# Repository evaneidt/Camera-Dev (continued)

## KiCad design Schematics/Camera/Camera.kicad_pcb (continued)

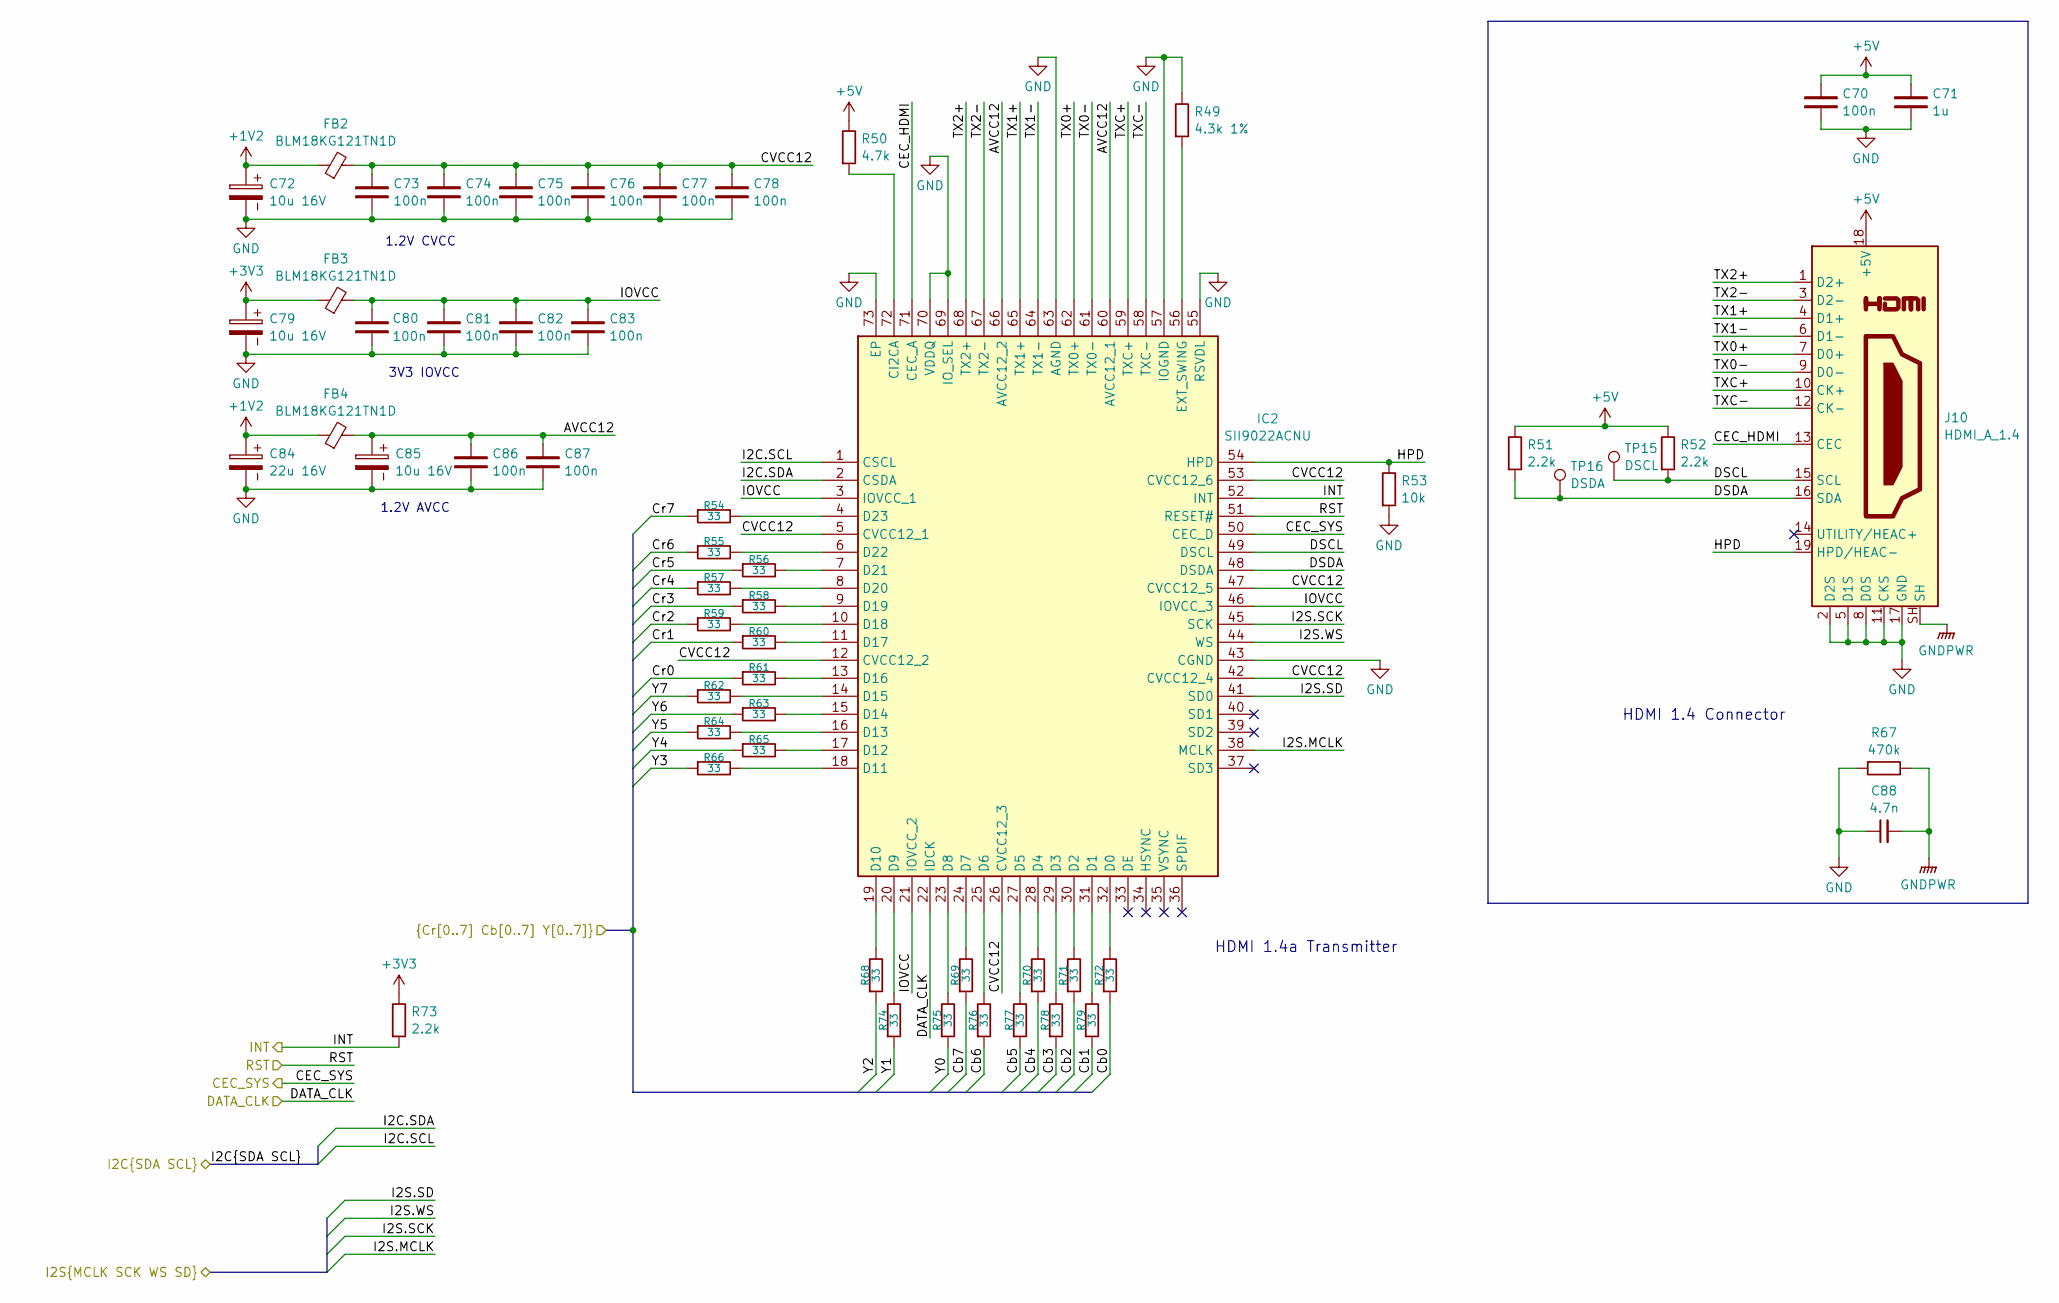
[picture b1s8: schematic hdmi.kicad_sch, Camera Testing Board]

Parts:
C70: 100n; C_0603_1608Metric
C71: 1u; C_0603_1608Metric
C72, C79, C85: 10u 16V; CP_EIA-3216-18_Kemet-A
C73, C74, C75, C76, C77, C78, C80, C81, C82, C83, C86, C87: 100n; C_0402_1005Metric
C84: 22u 16V; CP_EIA-3528-21_Kemet-B
C88: 4.7n; C_0603_1608Metric
FB2, FB3, FB4: BLM18KG121TN1D; L_0603_1608Metric
IC2: SII9022ACNU; QFN50P1000X1000X90-73N-D; Manufacturer_Part_Number SII9022ACNU
J10: HDMI_A_1.4; AMPHENOL_10029449-111RLF
R49: 4.3k 1%; R_0603_1608Metric
R50: 4.7k; R_0603_1608Metric
R51, R52, R73: 2.2k; R_0603_1608Metric
R53: 10k; R_0603_1608Metric
R54, R55, R56, R57, R58, R59, R60, R61, R62, R63, R64, R65, R66, R68, R69, R70, R71, R72, R74, R75, R76, R77, R78, R79: 33; R_0201_0603Metric
R67: 470k; R_0603_1608Metric
TP15: DSCL; TestPoint_Keystone_5000-5004_Miniature
TP16: DSDA; TestPoint_Keystone_5000-5004_Miniature

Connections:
+1V2: C72.1, C84.1, FB2.1, FB4.1; also elsewhere on the board
+3V3: C79.1, FB3.1, R73.2; also elsewhere on the board
+5V: C70.2, C71.2, J10.18 (+5V), R50.2, R51.2, R52.2; also elsewhere on the board
/HDMI/AVCC12: C85.1, C86.2, C87.2, FB4.2, IC2.60 (AVCC12_1), IC2.66 (AVCC12_2)
/HDMI/CEC_HDMI: IC2.71 (CEC_A), J10.13 (CEC)
/HDMI/CEC_SYS: IC2.50 (CEC_D); also elsewhere on the board
/HDMI/CVCC12: C73.2, C74.2, C75.2, C76.2, C77.2, C78.2, FB2.2, IC2.5 (CVCC12_1), IC2.12 (CVCC12_2), IC2.26 (CVCC12_3), IC2.42 (CVCC12_4), IC2.47 (CVCC12_5), IC2.53 (CVCC12_6)
/HDMI/Cb0: R72.1; also elsewhere on the board
/HDMI/Cb1: R79.1; also elsewhere on the board
/HDMI/Cb2: R71.1; also elsewhere on the board
/HDMI/Cb3: R78.1; also elsewhere on the board
/HDMI/Cb4: R70.1; also elsewhere on the board
/HDMI/Cb5: R77.1; also elsewhere on the board
/HDMI/Cb6: R76.1; also elsewhere on the board
/HDMI/Cb7: R69.1; also elsewhere on the board
/HDMI/Cr0: R61.1; also elsewhere on the board
/HDMI/Cr1: R60.1; also elsewhere on the board
/HDMI/Cr2: R59.1; also elsewhere on the board
/HDMI/Cr3: R58.1; also elsewhere on the board
/HDMI/Cr4: R57.1; also elsewhere on the board
/HDMI/Cr5: R56.1; also elsewhere on the board
/HDMI/Cr6: R55.1; also elsewhere on the board
/HDMI/Cr7: R54.1; also elsewhere on the board
/HDMI/DATA_CLK: IC2.22 (IDCK); also elsewhere on the board
/HDMI/DSCL: IC2.49 (DSCL), J10.15 (SCL), R52.1, TP15.1
/HDMI/DSDA: IC2.48 (DSDA), J10.16 (SDA), R51.1, TP16.1
/HDMI/HPD: IC2.54 (HPD), J10.19 (HPD/HEAC-), R53.2
/HDMI/I2C.SCL: IC2.1 (CSCL); also elsewhere on the board
/HDMI/I2C.SDA: IC2.2 (CSDA); also elsewhere on the board
/HDMI/I2S.MCLK: IC2.38 (MCLK); also elsewhere on the board
/HDMI/I2S.SCK: IC2.45 (SCK); also elsewhere on the board
/HDMI/I2S.SD: IC2.41 (SD0); also elsewhere on the board
/HDMI/I2S.WS: IC2.44 (WS); also elsewhere on the board
/HDMI/INT: IC2.52 (INT), R73.1; also elsewhere on the board
/HDMI/IOVCC: C80.2, C81.2, C82.2, C83.2, FB3.2, IC2.3 (IOVCC_1), IC2.21 (IOVCC_2), IC2.46 (IOVCC_3)
/HDMI/RST: IC2.51 (RESET#); also elsewhere on the board
/HDMI/TX0+: IC2.62 (TX0+), J10.7 (D0+)
/HDMI/TX0-: IC2.61 (TX0-), J10.9 (D0-)
/HDMI/TX1+: IC2.65 (TX1+), J10.4 (D1+)
/HDMI/TX1-: IC2.64 (TX1-), J10.6 (D1-)
/HDMI/TX2+: IC2.68 (TX2+), J10.1 (D2+)
/HDMI/TX2-: IC2.67 (TX2-), J10.3 (D2-)
/HDMI/TXC+: IC2.59 (TXC+), J10.10 (CK+)
/HDMI/TXC-: IC2.58 (TXC-), J10.12 (CK-)
/HDMI/Y0: R75.1; also elsewhere on the board
/HDMI/Y1: R74.1; also elsewhere on the board
/HDMI/Y2: R68.1; also elsewhere on the board
/HDMI/Y3: R66.1; also elsewhere on the board
/HDMI/Y4: R65.1; also elsewhere on the board
/HDMI/Y5: R64.1; also elsewhere on the board
/HDMI/Y6: R63.1; also elsewhere on the board
/HDMI/Y7: R62.1; also elsewhere on the board
GND: C70.1, C71.1, C72.2, C73.1, C74.1, C75.1, C76.1, C77.1, C78.1, C79.2, C80.1, C81.1, C82.1, C83.1, C84.2, C85.2, C86.1, C87.1, C88.1, IC2.43 (CGND), IC2.55 (RSVDL), IC2.57 (IOGND), IC2.63 (AGND), IC2.69 (IO_SEL), IC2.70 (VDDQ), IC2.73 (EP), J10.2 (D2S), J10.5 (D1S), J10.8 (D0S), J10.11 (CKS), J10.17 (GND), R49.2, R53.1, R67.1; also elsewhere on the board
GNDPWR: C88.2, J10.SH, R67.2; also elsewhere on the board
unnamed: IC2.72 (CI2CA), R50.1
unnamed: IC2.32 (D0), R72.2
unnamed: IC2.31 (D1), R79.2
unnamed: IC2.30 (D2), R71.2
unnamed: IC2.29 (D3), R78.2
unnamed: IC2.28 (D4), R70.2
unnamed: IC2.27 (D5), R77.2
unnamed: IC2.25 (D6), R76.2
unnamed: IC2.24 (D7), R69.2
unnamed: IC2.23 (D8), R75.2
unnamed: IC2.20 (D9), R74.2
unnamed: IC2.19 (D10), R68.2
unnamed: IC2.18 (D11), R66.2
unnamed: IC2.17 (D12), R65.2
unnamed: IC2.16 (D13), R64.2
unnamed: IC2.15 (D14), R63.2
unnamed: IC2.14 (D15), R62.2
unnamed: IC2.13 (D16), R61.2
unnamed: IC2.11 (D17), R60.2
unnamed: IC2.10 (D18), R59.2
unnamed: IC2.9 (D19), R58.2
unnamed: IC2.8 (D20), R57.2
unnamed: IC2.7 (D21), R56.2
unnamed: IC2.6 (D22), R55.2
unnamed: IC2.4 (D23), R54.2
unnamed: IC2.56 (EXT_SWING), R49.1

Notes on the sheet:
1.2V CVCC
HDMI 1.4a Transmitter
1.2V AVCC
HDMI 1.4 Connector
3V3 IOVCC

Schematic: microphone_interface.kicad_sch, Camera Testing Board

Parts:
C32, C33, C36: 100n; C_0603_1608Metric
C34, C35: 10u 16V; CP_EIA-3216-18_Kemet-A
D1, D2: LED; LED_0603_1608Metric
MK1, MK2: ICS-43434; InvenSense_ICS-43434-6_3.5x2.65mm
R21, R23: 0; R_0603_1608Metric
R22: 10k; R_0603_1608Metric
R24, R25, R26, R27: 33; R_0402_1005Metric
R28, R29: 470; R_0603_1608Metric
TP10: VBIAS; TestPoint_Keystone_5000-5004_Miniature
U7: PCM1780; SSOP-16_3.9x4.9mm_P0.635mm
U8: RCJ-2223; DUALRCA

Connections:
+3V3: C32.2, C33.2, MK1.5 (VDD), MK2.2 (LR), MK2.5 (VDD); also elsewhere on the board
+5V: C35.1, C36.2, U7.11 (Vcc); also elsewhere on the board
/HDMI/I2S.MCLK: R25.1; also elsewhere on the board
/HDMI/I2S.SCK: MK1.4 (SCK), MK2.4 (SCK), R24.1; also elsewhere on the board
/HDMI/I2S.SD: R21.2, R22.2, R23.2, R27.1; also elsewhere on the board
/HDMI/I2S.WS: MK1.1 (WS), MK2.1 (WS), R26.1; also elsewhere on the board
/Microcontroller/DAC.CLK: U7.3 (MC); also elsewhere on the board
/Microcontroller/DAC.MOSI: U7.4 (MD); also elsewhere on the board
/Microcontroller/DAC.nCS: U7.2 (~MS); also elsewhere on the board
/Microphone Interface/Audio Filtering/L_IN: U7.15 (V_{OUT}L); also elsewhere on the board
/Microphone Interface/Audio Filtering/L_OUT: U8.P$2 (BTM); also elsewhere on the board
/Microphone Interface/Audio Filtering/R_IN: U7.14 (V_{OUT}R); also elsewhere on the board
/Microphone Interface/Audio Filtering/R_OUT: U8.P$3 (TOP); also elsewhere on the board
/Microphone Interface/VBIAS: C34.1, TP10.1, U7.13 (V_{COM}); also elsewhere on the board
GND: C32.1, C33.1, C34.2, C35.2, C36.1, D1.1 (K), D2.1 (K), MK1.2 (LR), MK1.3 (GND), MK2.3 (GND), R22.1, U7.12 (AGND), U8.P$1 (GND); also elsewhere on the board
unnamed: D1.2 (A), R28.1
unnamed: D2.2 (A), R29.1
unnamed: MK1.6 (SD), R21.1
unnamed: MK2.6 (SD), R23.1
unnamed: R24.2, U7.7 (BCK)
unnamed: R27.2, U7.6 (DATA)
unnamed: R26.2, U7.8 (LRCK)
unnamed: R25.2, U7.5 (SCK)
unnamed: R29.2, U7.1 (ZEROL)
unnamed: R28.2, U7.16 (ZEROR)

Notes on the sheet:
f_s = 44.1 kHz I2S SCK = 64 * f_s = 2.8224 MHz DAC System Clock = MCLK = 256 * f_s = 11.290 MHz I2S WS = f_s = 44.1 kHz MIC STBY = I2S SCK < 200 kHz --> Pull WS & SCK to GND
Right Channel
Left Channel
Audio DAC
Red
I2S Signals
Microphones
RCA Audio Outputs
Clock Generation
Zero LEDs

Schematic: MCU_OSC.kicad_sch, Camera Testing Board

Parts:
C31: 100n; C_0603_1608Metric
X1: ECS-TXO-2520MV-500-AN-TR; Oscillator_SMD_ECS_2520MV-xxx-xx-4Pin_2.5x2.0mm
X2: ASEKDVAIG-32.768KHZ-KC-T3; Oscillator_SMD_Abracon_ASE-4Pin_3.2x2.5mm

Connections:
+3V3: C31.2, X1.1 (Tri-State), X1.4 (VDD), X2.1 (EN), X2.4 (Vdd); also elsewhere on the board
/Microcontroller/32.768kHz_OSC: X2.3 (OUT); also elsewhere on the board
/Microcontroller/50MHz_OSC: X1.3 (OUT); also elsewhere on the board
GND: C31.1, X1.2 (GND), X2.2 (GND); also elsewhere on the board

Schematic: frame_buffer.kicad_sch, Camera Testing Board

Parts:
C51, C52, C53, C54, C55: 100n; C_0603_1608Metric
C56, C57, C58, C59, C60, C61, C62, C63, C64, C100: 100n; C_0402_1005Metric
C98, C99: 1u; C_0603_1608Metric
IC1: IS42S32400F-6TL-TR; SOP50P1176X120-86N; Mouser Part Number 870-IS42S32400F6TLTR
R42: 10k; R_0603_1608Metric
R83, R84, R85, R86, R87, R88, R89, R90: 1k; R_0402_1005Metric
U15, U16, U17, U18, U19: 74LV595; SOIC-16_3.9x9.9mm_P1.27mm

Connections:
+3V3: C51.2, C52.2, C53.2, C54.2, C55.2, C56.2, C57.2, C58.2, C59.2, C60.2, C61.2, C62.2, C63.2, C64.2, C98.2, C99.2, C100.2, IC1.1 (VDD_1), IC1.3 (VDDQ_1), IC1.9 (VDDQ_2), IC1.15 (VDD_2), IC1.29 (VDD_3), IC1.35 (VDDQ_3), IC1.41 (VDDQ_4), IC1.43 (VDD_4), IC1.49 (VDDQ_5), IC1.55 (VDDQ_6), IC1.75 (VDDQ_7), IC1.81 (VDDQ_8), R42.2, U15.16 (VCC), U16.16 (VCC), U17.16 (VCC), U18.16 (VCC), U19.16 (VCC); also elsewhere on the board
/HDMI/Cb0: IC1.31 (DQ16), U17.15 (QA); also elsewhere on the board
/HDMI/Cb1: IC1.33 (DQ17), U17.1 (QB); also elsewhere on the board
/HDMI/Cb2: IC1.34 (DQ18), U17.2 (QC); also elsewhere on the board
/HDMI/Cb3: IC1.36 (DQ19), U17.3 (QD); also elsewhere on the board
/HDMI/Cb4: IC1.37 (DQ20), U17.4 (QE); also elsewhere on the board
/HDMI/Cb5: IC1.39 (DQ21), U17.5 (QF); also elsewhere on the board
/HDMI/Cb6: IC1.40 (DQ22), U17.6 (QG); also elsewhere on the board
/HDMI/Cb7: IC1.42 (DQ23), U17.7 (QH); also elsewhere on the board
/HDMI/Cr0: IC1.74 (DQ8), U19.15 (QA); also elsewhere on the board
/HDMI/Cr1: IC1.76 (DQ9), U19.1 (QB); also elsewhere on the board
/HDMI/Cr2: IC1.77 (DQ10), U19.2 (QC); also elsewhere on the board
/HDMI/Cr3: IC1.79 (DQ11), U19.3 (QD); also elsewhere on the board
/HDMI/Cr4: IC1.80 (DQ12), U19.4 (QE); also elsewhere on the board
/HDMI/Cr5: IC1.82 (DQ13), U19.5 (QF); also elsewhere on the board
/HDMI/Cr6: IC1.83 (DQ14), U19.6 (QG); also elsewhere on the board
/HDMI/Cr7: IC1.85 (DQ15), U19.7 (QH); also elsewhere on the board
/HDMI/Y0: IC1.45 (DQ24), U15.15 (QA); also elsewhere on the board
/HDMI/Y1: IC1.47 (DQ25), U15.1 (QB); also elsewhere on the board
/HDMI/Y2: IC1.48 (DQ26), U15.2 (QC); also elsewhere on the board
/HDMI/Y3: IC1.50 (DQ27), U15.3 (QD); also elsewhere on the board
/HDMI/Y4: IC1.51 (DQ28), U15.4 (QE); also elsewhere on the board
/HDMI/Y5: IC1.53 (DQ29), U15.5 (QF); also elsewhere on the board
/HDMI/Y6: IC1.54 (DQ30), U15.6 (QG); also elsewhere on the board
/HDMI/Y7: IC1.56 (DQ31), U15.7 (QH); also elsewhere on the board
/Memory/A.CLK: U16.11 (SRCLK), U16.12 (RCLK), U18.11 (SRCLK), U18.12 (RCLK); also elsewhere on the board
/Memory/A.IN: U16.14 (SER); also elsewhere on the board
/Memory/A.nOE: U16.13 (~OE), U18.13 (~OE); also elsewhere on the board
/Memory/ADDR0: IC1.22 (BA0), U16.15 (QA)
/Memory/ADDR1: IC1.23 (BA1), U16.1 (QB)
/Memory/ADDR2: IC1.25 (A0), U16.2 (QC)
/Memory/ADDR3: IC1.26 (A1), U16.3 (QD)
/Memory/ADDR4: IC1.27 (A2), U16.4 (QE)
/Memory/ADDR5: IC1.60 (A3), U16.5 (QF)
/Memory/ADDR6: IC1.61 (A4), U16.6 (QG)
/Memory/ADDR7: IC1.62 (A5), U16.7 (QH)
/Memory/ADDR8: IC1.63 (A6), U18.15 (QA)
/Memory/ADDR9: IC1.64 (A7), U18.1 (QB)
/Memory/ADDR10: IC1.65 (A8), U18.2 (QC)
/Memory/ADDR11: IC1.66 (A9), U18.3 (QD)
/Memory/ADDR12: IC1.24 (A10), U18.4 (QE)
/Memory/ADDR13: IC1.21 (A11), U18.5 (QF)
/Memory/D.CLK: U15.11 (SRCLK), U15.12 (RCLK), U17.11 (SRCLK), U17.12 (RCLK), U19.11 (SRCLK), U19.12 (RCLK); also elsewhere on the board
/Memory/D.IN: U15.14 (SER); also elsewhere on the board
/Memory/D.nOE: U15.13 (~OE), U17.13 (~OE), U19.13 (~OE); also elsewhere on the board
/Memory/Frame Buffer/ADDR14: U18.6 (QG)
/Memory/Frame Buffer/ADDR15: U18.7 (QH)
/Memory/RAM.CLK: IC1.68 (CLK); also elsewhere on the board
/Memory/RAM.nCAS: IC1.18 (~CAS); also elsewhere on the board
/Memory/RAM.nDQM: IC1.16 (DQM0), IC1.28 (DQM2), IC1.59 (DQM3), IC1.71 (DQM1); also elsewhere on the board
/Memory/RAM.nPD: IC1.67 (CKE); also elsewhere on the board
/Memory/RAM.nRAS: IC1.19 (~RAS); also elsewhere on the board
/Memory/RAM.nWE: IC1.17 (~WE); also elsewhere on the board
/Memory/SR.nCLR: R42.1, U15.10 (~SRCLR), U16.10 (~SRCLR), U17.10 (~SRCLR), U18.10 (~SRCLR), U19.10 (~SRCLR); also elsewhere on the board
GND: C51.1, C52.1, C53.1, C54.1, C55.1, C56.1, C57.1, C58.1, C59.1, C60.1, C61.1, C62.1, C63.1, C64.1, C98.1, C99.1, C100.1, IC1.6 (VSSQ_1), IC1.12 (VSSQ_2), IC1.20 (~CS), IC1.32 (VSSQ_3), IC1.38 (VSSQ_4), IC1.44 (VSS_1), IC1.46 (VSSQ_5), IC1.52 (VSSQ_6), IC1.58 (VSS_2), IC1.72 (VSS_3), IC1.78 (VSSQ_7), IC1.84 (VSSQ_8), IC1.86 (VSS_4), R83.2, R84.2, R85.2, R86.2, R87.2, R88.2, R89.2, R90.2, U15.8 (GND), U16.8 (GND), U17.8 (GND), U18.8 (GND), U19.8 (GND); also elsewhere on the board
unnamed: IC1.2 (DQ0), R90.1
unnamed: IC1.4 (DQ1), R89.1
unnamed: IC1.5 (DQ2), R88.1
unnamed: IC1.7 (DQ3), R87.1
unnamed: IC1.8 (DQ4), R86.1
unnamed: IC1.10 (DQ5), R85.1
unnamed: IC1.11 (DQ6), R84.1
unnamed: IC1.13 (DQ7), R83.1
unnamed: U15.9 (QH'), U17.14 (SER)
unnamed: U16.9 (QH'), U18.14 (SER)
unnamed: U17.9 (QH'), U19.14 (SER)

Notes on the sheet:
SR_CTRL
Byte 0
Byte 1
Byte 2
RAM Caps
SR Caps
Address Registers
Frame Buffer 128Mbit DRAM
RAM_CTRL
Data Registers

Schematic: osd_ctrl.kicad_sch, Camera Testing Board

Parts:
C15: 100n; C_0603_1608Metric
R9: 1k; R_0603_1608Metric
R10: 15k; R_0603_1608Metric
R11: 27k; R_0603_1608Metric
R12: 18k; R_0603_1608Metric
R13: 6.8k; R_0603_1608Metric
TP8: OSD_IN; TestPoint_Keystone_5000-5004_Miniature
TP9: OSD_OUT; TestPoint_Keystone_5000-5004_Miniature
U5: TMUX1208RSVR; RSV16_TEX

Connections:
+3V3: C15.2, U5.11 (VDD); also elsewhere on the board
/Camera Interface/OSD CTRL/Center_Res: R12.2, U5.2 (S1)
/Camera Interface/OSD CTRL/Down_Res: R9.2, R10.1, R11.1, R13.1, U5.5 (S4)
/Camera Interface/OSD CTRL/Left_Res: R11.2, R12.1, U5.4 (S3)
/Camera Interface/OSD CTRL/OSD_IN: R9.1, TP8.1; also elsewhere on the board
/Camera Interface/OSD CTRL/OSD_OUT: TP9.1, U5.6 (D); also elsewhere on the board
/Camera Interface/OSD CTRL/Right_Res: R13.2, U5.10 (S5)
/Camera Interface/OSD CTRL/Up_Res: R10.2, U5.3 (S2)
/Camera Interface/OSD.A0: U5.15 (A0); also elsewhere on the board
/Camera Interface/OSD.A1: U5.14 (A1); also elsewhere on the board
/Camera Interface/OSD.A2: U5.13 (A2); also elsewhere on the board
/Camera Interface/OSD.EN: U5.16 (EN); also elsewhere on the board
GND: C15.1, U5.12 (GND); also elsewhere on the board

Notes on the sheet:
Resistor Network
Analog MUX 8:1

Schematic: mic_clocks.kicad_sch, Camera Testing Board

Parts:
C44, C45, C48: 100n; C_0603_1608Metric
C46, C47: 30p; C_0402_1005Metric
R38: 2.2M; R_0603_1608Metric
R39: 470; R_0603_1608Metric
R40, R41: 10k; R_0603_1608Metric
TP13: MK_XIN; TestPoint_Keystone_5000-5004_Miniature
TP14: MK_XOUT; TestPoint_Keystone_5000-5004_Miniature
U10: 74LVC1404; SSOP-8_2.95x2.8mm_P0.65mm
U11: 74LV393; SOIC-14_3.9x8.7mm_P1.27mm
U12: 74LVC1G86; SOT-353_SC-70-5
Y2: 11.2896 MHz; Crystal_SMD_Abracon_ABM3-2Pin_5.0x3.2mm

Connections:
+3V3: C44.2, C45.2, C48.2, U10.8 (VCC), U11.14 (VCC), U12.1, U12.5 (VCC); also elsewhere on the board
/HDMI/I2S.MCLK: U10.5 (Y), U11.1 (CP); also elsewhere on the board
/HDMI/I2S.SCK: U11.4 (Q1); also elsewhere on the board
/HDMI/I2S.WS: U11.8 (Q3); also elsewhere on the board
/Microphone Interface/Microphone Clocks/CLR: R41.2, U11.2 (MR), U11.12 (MR), U12.4
/Microphone Interface/Microphone Clocks/CTRL: R40.2, U10.1 (CTRL), U12.2; also elsewhere on the board
/Microphone Interface/Microphone Clocks/OSCOUT: U10.6 (A), U10.7 (OSCOUT)
/Microphone Interface/Microphone Clocks/XIN: C46.1, R38.1, TP13.1, U10.3 (XIN), Y2.1
/Microphone Interface/Microphone Clocks/XOUT: R38.2, R39.2, TP14.1, U10.2 (XOUT)
/Microphone Interface/Microphone Clocks/div2: U11.3 (Q0)
/Microphone Interface/Microphone Clocks/div8: U11.5 (Q2)
/Microphone Interface/Microphone Clocks/div16: U11.6 (Q3), U11.13 (CP)
/Microphone Interface/Microphone Clocks/div32: U11.11 (Q0)
/Microphone Interface/Microphone Clocks/div64: U11.10 (Q1)
/Microphone Interface/Microphone Clocks/div128: U11.9 (Q2)
GND: C44.1, C45.1, C46.2, C47.2, C48.1, R40.1, R41.1, U10.4 (GND), U11.7 (GND), U12.3 (GND); also elsewhere on the board
unnamed: C47.1, R39.1, Y2.2

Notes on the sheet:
f_s = 44.1 kHz I2S SCK = 64 * f_s = 2.8224 MHz DAC System Clock = MCLK = 256 * f_s = 11.2896 MHz I2S WS = f_s = 44.1 kHz MIC STBY = I2S SCK < 200 kHz --> Pull WS & SCK to GND
Clear Signal
Stage 2
I2S Clock Outputs
Clock Divider
Stage 1
(~CTRL)
MCLK CTRL Input
MCLK Generator

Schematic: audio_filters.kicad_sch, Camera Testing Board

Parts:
C37: 100n; C_0603_1608Metric
C38, C41: 1n; C_0603_1608Metric
C39, C42: 10u 16V; CP_EIA-3216-18_Kemet-A
C40, C43: 3.9n; C_0603_1608Metric
R30, R34: 2.2k; R_0603_1608Metric
R31, R35: 5.1k; R_0603_1608Metric
R32, R36: 4.7k; R_0603_1608Metric
R33, R37: 1k; R_0603_1608Metric
TP11: L_IN; TestPoint_Keystone_5000-5004_Miniature
TP12: R_IN; TestPoint_Keystone_5000-5004_Miniature
U9: OPA2356xxD; SOIC-8_3.9x4.9mm_P1.27mm

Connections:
+5V: C37.2, U9.8 (V+); also elsewhere on the board
/Microphone Interface/Audio Filtering/L_IN: R31.1, TP11.1; also elsewhere on the board
/Microphone Interface/Audio Filtering/L_OUT: C39.2, R33.2; also elsewhere on the board
/Microphone Interface/Audio Filtering/R_IN: R35.1, TP12.1; also elsewhere on the board
/Microphone Interface/Audio Filtering/R_OUT: C42.2, R37.2; also elsewhere on the board
/Microphone Interface/VBIAS: U9.3 (+), U9.5 (+); also elsewhere on the board
GND: C37.1, C40.2, C43.2, R33.1, R37.1, U9.4 (V-); also elsewhere on the board
unnamed: C38.1, C39.1, R30.2, U9.1
unnamed: C40.1, R30.1, R31.2, R32.1
unnamed: C41.1, C42.1, R34.2, U9.7
unnamed: C43.1, R34.1, R35.2, R36.1
unnamed: C38.2, R32.2, U9.2 (-)
unnamed: C41.2, R36.2, U9.6 (-)

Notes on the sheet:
LPF f_c: 25 kHz HPF f_c: 16 Hz Gain: -7.3dB (converted to RCA voltage levels)

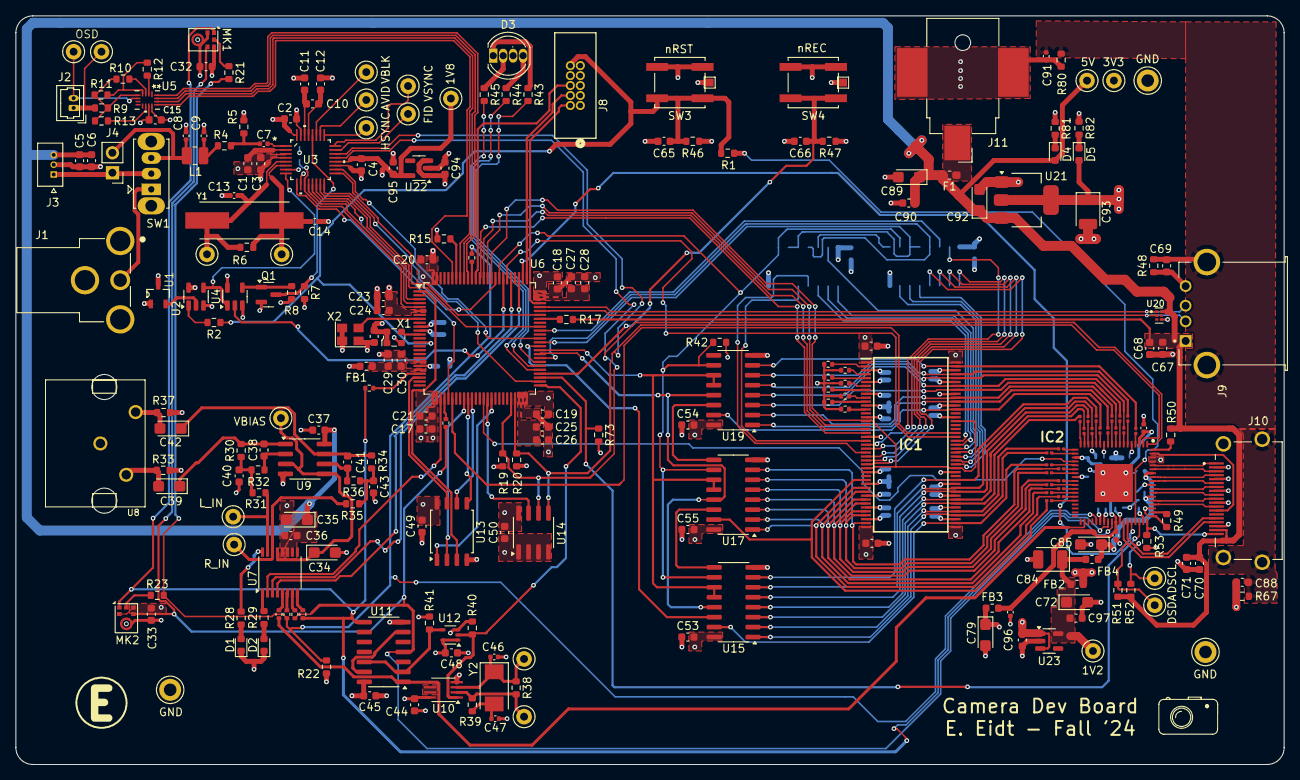
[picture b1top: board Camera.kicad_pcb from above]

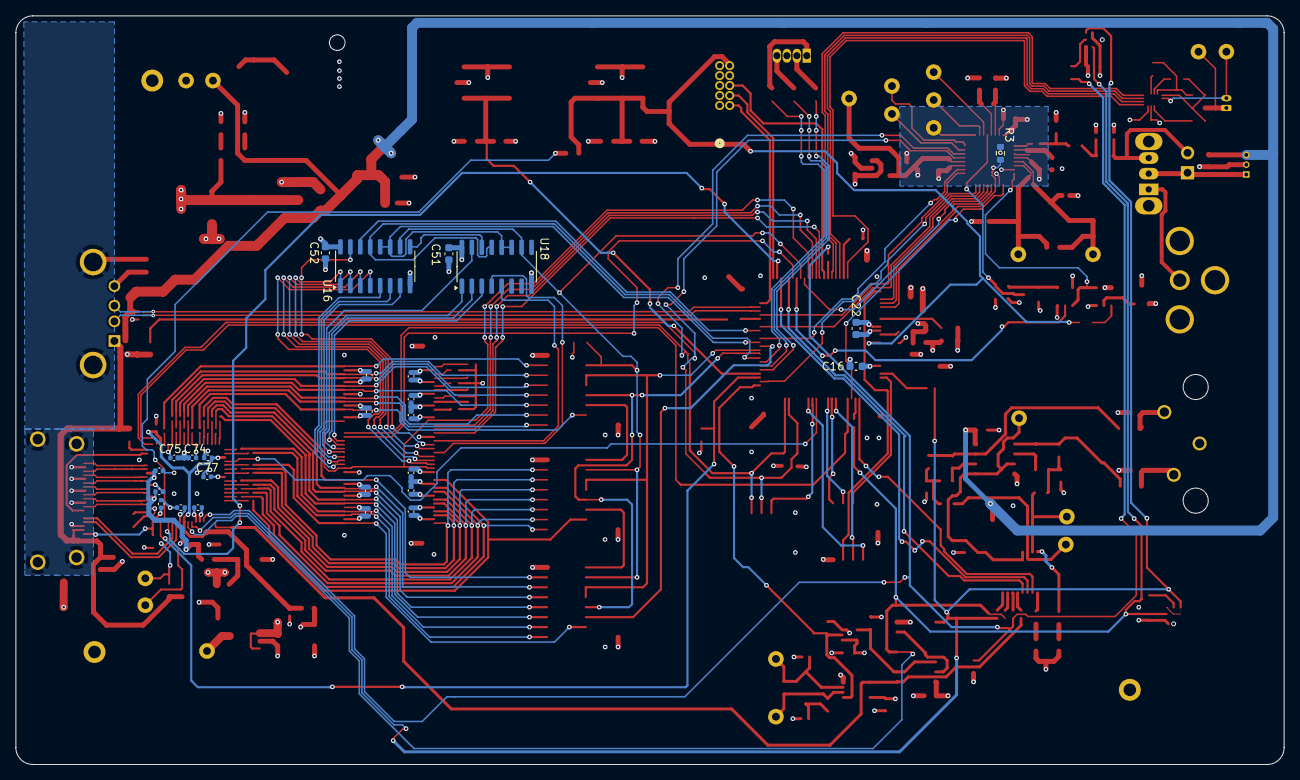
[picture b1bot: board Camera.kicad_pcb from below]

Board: 4 copper layers, 161.8 x 95.5 mm, 269 parts (26 on the bottom side), 226 nets.

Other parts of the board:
PAD1, PAD2: TestPoint_Pad_1.0x1.0mm

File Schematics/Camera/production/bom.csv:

Designator,Footprint,Quantity,Value,LCSC Part #
"C1, C15, C18, C19, C2, C20, C21, C22, C24, C25, C27, C3, C30, C31, C32, C33, C36, C37, C4, C44, C45, C48, C49, C5, C50, C51, C52, C53, C54, C55, C65, C66, C67, C70, C90",0603,35,100n,
"C10, C11, C12, C16, C23, C29, C6, C68, C71, C94, C95, C96, C97, C98, C99",0603,15,1u,
"C100, C56, C57, C58, C59, C60, C61, C62, C63, C64, C73, C74, C75, C76, C77, C78, C80, C81, C82, C83, C86, C87",0402,22,100n,
"C13, C14",0402,2,24p,
C17,0603,1,4.7u,
"C26, C28",0603,2,2.2u,
"C34, C35, C39, C42, C72, C79, C85, C89, C92",CP_EIA-3216-18_Kemet-A,9,10u 16V,
"C38, C41",0603,2,1n,
"C40, C43",0603,2,3.9n,
"C46, C47",0402,2,30p,
"C69, C88",0603,2,4.7n,
"C7, C8, C9",0402,3,180p,
"C84, C93",CP_EIA-3528-21_Kemet-B,2,22u 16V,
C91,0402,1,100p,
"D1, D2, D4, D5",0603,4,LED,
D3,LED_D5.0mm-4_RGB,1,LED_RGBK,
F1,0603,1,2A,
"FB1, FB2, FB3, FB4",0603,4,BLM18KG121TN1D,
IC1,SOP50P1176X120-86N,1,IS42S32400F-6TL-TR,
IC2,QFN50P1000X1000X90-73N-D,1,SII9022ACNU,
J1,CUI_RCJ-014,1,RCJ-014,
J10,AMPHENOL_10029449-111RLF,1,HDMI_A_1.4,
J11,BarrelJack_CUI_PJ-036AH-SMT_Horizontal,1,Barrel_Jack_MountingPin,
J2,Molex_PicoBlade_53047-0210_1x02_P1.25mm_Vertical,1,53047-0210,
J3,MOLEX_530470310,1,530470310,
J4,PinHeader_1x02_P2.54mm_Vertical,1,PINHD_1x2_Male,
J8,CONN_3220-10-0100-00_CNC,1,3220-10-0100-00,
J9,AMPHENOL_UE27AC5410H,1,UE27AC5410H,
L1,1008,1,2.2u,
"MK1, MK2",InvenSense_ICS-43434-6_3.5x2.65mm,2,ICS-43434,
Q1,SOT-23,1,BSS138,
"R1, R17, R2, R21, R23",0603,5,0,
R10,0603,1,15k,
R11,0603,1,27k,
R12,0603,1,18k,
R13,0603,1,6.8k,
"R14, R16, R18, R24, R25, R26, R27",0402,7,33,
"R15, R22, R3, R40, R41, R42, R46, R47, R53, R7, R8",0603,11,10k,
"R19, R20, R32, R36, R50",0603,5,4.7k,
"R28, R29, R39, R81",0603,4,470,
"R30, R34, R51, R52, R73",0603,5,2.2k,
"R31, R35",0603,2,5.1k,
"R33, R37, R9",0603,3,1k,
R38,0603,1,2.2M,
"R4, R5",0603,2,39,
"R43, R44, R45, R82",0603,4,330,
"R48, R67",0603,2,470k,
R49,0603,1,4.3k 1%,
"R54, R55, R56, R57, R58, R59, R60, R61, R62, R63, R64, R65, R66, R68, R69, R70, R71, R72, R74, R75, R76, R77, R78, R79",0201,24,33,
R6,0603,1,100k,
R80,0603,1,47,
"R83, R84, R85, R86, R87, R88, R89, R90",0402,8,1k,
SW1,SW_Slide_SPDT_Straight_CK_OS102011MS2Q,1,SW_SPDT,
"SW3, SW4",SW_Push_1P1T_NO_CK_KSC7xxJ,2,Push_Button_W12mm,
TP1,TestPoint_Keystone_5000-5004_Miniature,1,HSYNC,
TP10,TestPoint_Keystone_5000-5004_Miniature,1,VBIAS,
TP11,TestPoint_Keystone_5000-5004_Miniature,1,L_IN,
TP12,TestPoint_Keystone_5000-5004_Miniature,1,R_IN,
TP13,TestPoint_Keystone_5000-5004_Miniature,1,MK_XIN,
TP14,TestPoint_Keystone_5000-5004_Miniature,1,MK_XOUT,
TP15,TestPoint_Keystone_5000-5004_Miniature,1,DSCL,
TP16,TestPoint_Keystone_5000-5004_Miniature,1,DSDA,
TP17,TestPoint_Keystone_5000-5004_Miniature,1,5V,
TP18,TestPoint_Keystone_5000-5004_Miniature,1,3V3,
TP19,TestPoint_Keystone_5000-5004_Miniature,1,1V8,
TP2,TestPoint_Keystone_5000-5004_Miniature,1,VSYNC,
"TP20, TP21, TP22",TestPoint_Keystone_5010-5014_Multipurpose,3,GND,
TP23,TestPoint_Keystone_5000-5004_Miniature,1,1V2,
TP3,TestPoint_Keystone_5000-5004_Miniature,1,AVID,
TP4,TestPoint_Keystone_5000-5004_Miniature,1,FID,
TP5,TestPoint_Keystone_5000-5004_Miniature,1,VBLK,
TP6,TestPoint_Keystone_5000-5004_Miniature,1,CAM_X1,
TP7,TestPoint_Keystone_5000-5004_Miniature,1,CAM_X2,
TP8,TestPoint_Keystone_5000-5004_Miniature,1,OSD_IN,
TP9,TestPoint_Keystone_5000-5004_Miniature,1,OSD_OUT,
U1,SOT95P232X110-3N,1,MIC803-29D2VM3TR,MIC803-29D2VM3TR
U10,SSOP-8_2.95x2.8mm_P0.65mm,1,74LVC1404,
U11,SOIC-14_3.9x8.7mm_P1.27mm,1,74LV393,
U12,SOT-353_SC-70-5,1,74LVC1G86,
U13,SOIC-8_5.23x5.23mm_P1.27mm,1,W25Q16JVSS,
U14,SOIC-8_3.9x4.9mm_P1.27mm,1,M24C02-WMN,
"U15, U16, U17, U18, U19",SOIC-16_3.9x9.9mm_P1.27mm,5,74LV595,
"U2, U4",SOT-23-5,2,74LVC1G08,
U20,PSON50P145X100X60-6N,1,TPD4S012DRYR,
U21,SOT-223-3_TabPin2,1,AZ1117-3.3,
U22,SOT-23-5,1,MIC5504-1.8YM5,
U23,SOT-23-5,1,MIC5504-1.2YM5,
U3,PBS32,1,TVP5150AM1PBSR,
U5,RSV16_TEX,1,TMUX1208RSVR,
U6,LQFP-100_14x14mm_P0.5mm,1,STM32H7B0VBTx,
U7,SSOP-16_3.9x4.9mm_P0.635mm,1,PCM1780,
U8,DUALRCA,1,RCJ-2223,
U9,SOIC-8_3.9x4.9mm_P1.27mm,1,OPA2356xxD,
X1,Oscillator_SMD_ECS_2520MV-xxx-xx-4Pin_2.5x2.0mm,1,ECS-TXO-2520MV-500-AN-TR,
X2,Oscillator_SMD_Abracon_ASE-4Pin_3.2x2.5mm,1,ASEKDVAIG-32.768KHZ-KC-T3,
Y1,XTAL_ABLS2-14.31818MHZ-D4Y-T,1,14.31818MHz,
Y2,Crystal_SMD_Abracon_ABM3-2Pin_5.0x3.2mm,1,11.2896 MHz,

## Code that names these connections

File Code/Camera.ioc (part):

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Mcu.Name=STM32H7B0VBTx
Mcu.Package=LQFP100
Mcu.UserName=STM32H7B0VBTx
PA0.GPIOParameters=GPIO_Label
PA0.GPIO_Label=I2S WS
PA0.Mode=Half_Duplex_Slave_Rx
PA0.Signal=I2S6_WS
PA1.GPIOParameters=GPIO_Label
PA1.GPIO_Label=QSPI IO3
PA1.Mode=OCTOSPI2_IOL_Port1L
PA1.Signal=OCTOSPIM_P1_IO3
PA10.GPIOParameters=GPIO_Label
PA10.GPIO_Label=YOUT1
PA10.Mode=Slave_8_bits_Embedded_Synchro
PA10.Signal=DCMI_D1
PA11.GPIOParameters=GPIO_Label
PA11.GPIO_Label=USB DM
PA11.Mode=Host_FS
PA11.Signal=USB_OTG_HS_DM
PA12.GPIOParameters=GPIO_Label
PA12.GPIO_Label=USB DP
PA12.Mode=Host_FS
PA12.Signal=USB_OTG_HS_DP
PA13.GPIOParameters=GPIO_Label
PA13.GPIO_Label=SWDIO
PA13.Mode=Trace_Asynchronous_SW
PA13.Signal=DEBUG_JTMS-SWDIO
PA14.GPIOParameters=GPIO_Label
PA14.GPIO_Label=SWCLK
PA14.Mode=Trace_Asynchronous_SW
PA14.Signal=DEBUG_JTCK-SWCLK
PA15.GPIOParameters=GPIO_Label
PA15.GPIO_Label=HDMI CE
PA15.Mode=CEC_Activate
PA15.Signal=CEC
PA4.GPIOParameters=GPIO_Label
PA4.GPIO_Label=DAC nCS
PA4.Signal=GPIO_Output
PA5.GPIOParameters=GPIO_Label
PA5.GPIO_Label=I2S SCK
PA5.Mode=Half_Duplex_Slave_Rx
PA5.Signal=I2S6_CK
PA6.GPIOParameters=GPIO_Label
PA6.GPIO_Label=CAM CLK
PA6.Mode=Slave_8_bits_Embedded_Synchro
PA6.Signal=DCMI_PIXCLK
PA7.GPIOParameters=GPIO_Label
PA7.GPIO_Label=RAM CLK
PA7.Signal=S_TIM14_CH1
PA9.GPIOParameters=GPIO_Label
PA9.GPIO_Label=USB VBUS
PA9.Mode=Activate_VBUS_FS
PA9.Signal=USB_OTG_HS_VBUS
PB0.GPIOParameters=GPIO_Label
PB0.GPIO_Label=QSPI IO1
PB0.Mode=OCTOSPI2_IOL_Port1L
PB0.Signal=OCTOSPIM_P1_IO1
PB1.GPIOParameters=GPIO_Label
PB1.GPIO_Label=QSPI IO0
PB1.Mode=OCTOSPI2_IOL_Port1L
PB1.Signal=OCTOSPIM_P1_IO0
PB10.GPIOParameters=GPIO_Label
PB10.GPIO_Label=I2S SCL
PB10.Mode=I2C
PB10.Signal=I2C2_SCL
PB11.GPIOParameters=GPIO_Label
PB11.GPIO_Label=I2C SDA
PB11.Mode=I2C
PB11.Signal=I2C2_SDA
PB12.GPIOParameters=GPIO_Label
PB12.GPIO_Label=I2S MCLK CTRL
PB12.Signal=GPIO_Output
PB13.GPIOParameters=GPIO_Label
PB13.GPIO_Label=YOUT2
PB13.Mode=Slave_8_bits_Embedded_Synchro
PB13.Signal=DCMI_D2
PB14.GPIOParameters=GPIO_Label
PB14.GPIO_Label=HDMI INT
PB14.Signal=GPXTI14
PB15.GPIOParameters=GPIO_Label,GPIO_ModeDefaultEXTI
PB15.GPIO_Label=nREC
PB15.GPIO_ModeDefaultEXTI=GPIO_MODE_IT_FALLING
PB15.Signal=GPXTI15
PB2.GPIOParameters=GPIO_Label
PB2.GPIO_Label=QSPI CLK
PB2.Mode=O2_P1_CLK
PB2.Signal=OCTOSPIM_P1_CLK
PB3.GPIOParameters=GPIO_Label
PB3.GPIO_Label=SWO
PB3.Mode=Trace_Asynchronous_SW
PB3.Signal=DEBUG_JTDO-SWO
PB4.GPIOParameters=GPIO_Label
PB4.GPIO_Label=I2S SD
PB4.Mode=Half_Duplex_Slave_Rx
PB4.Signal=I2S6_SDI
PB5.GPIOParameters=GPIO_Label
PB5.GPIO_Label=OSD A2
PB5.Signal=GPIO_Output
PB6.GPIOParameters=GPIO_Label
PB6.GPIO_Label=OSD A1
PB6.Signal=GPIO_Output
PB7.GPIOParameters=GPIO_Label
PB7.GPIO_Label=OSD A0
PB7.Signal=GPIO_Output
PB8.GPIOParameters=GPIO_Label
PB8.GPIO_Label=OSD EN
PB8.Signal=GPIO_Output
PC0.GPIOParameters=GPIO_PuPd,GPIO_Label
PC0.GPIO_Label=DIP 1
PC0.GPIO_PuPd=GPIO_PULLDOWN
PC0.Signal=GPIO_Input
PC10.GPIOParameters=GPIO_Label
PC10.GPIO_Label=DAC CLK
PC10.Mode=TX_Only_Simplex_Unidirect_Master
PC10.Signal=SPI3_SCK
PC11.GPIOParameters=GPIO_PuPd,GPIO_Label
PC11.GPIO_Label=DIP 2
PC11.GPIO_PuPd=GPIO_PULLDOWN
PC11.Signal=GPIO_Input
PC12.GPIOParameters=GPIO_Label
PC12.GPIO_Label=DAC MOSI
PC12.Mode=TX_Only_Simplex_Unidirect_Master
PC12.Signal=SPI3_MOSI
PC14-OSC32_IN.GPIOParameters=GPIO_Label
PC14-OSC32_IN.GPIO_Label=LSE OSC
PC14-OSC32_IN.Mode=LSE-External-Clock-Source
PC14-OSC32_IN.Signal=RCC_OSC32_IN
PC2_C.GPIOParameters=GPIO_PuPd,GPIO_Label
PC2_C.GPIO_Label=DIP 3
PC2_C.GPIO_PuPd=GPIO_PULLDOWN
PC2_C.Signal=GPIO_Input
PC3_C.GPIOParameters=GPIO_PuPd,GPIO_Label
PC3_C.GPIO_Label=DIP 4
PC3_C.GPIO_PuPd=GPIO_PULLDOWN
PC3_C.Signal=GPIO_Input
PC4.GPIOParameters=GPIO_PuPd,GPIO_Label
PC4.GPIO_Label=DIP 5
PC4.GPIO_PuPd=GPIO_PULLDOWN
PC4.Signal=GPIO_Input
PC5.GPIOParameters=GPIO_PuPd,GPIO_Label
PC5.GPIO_Label=DIP 6
PC5.GPIO_PuPd=GPIO_PULLDOWN
PC5.Signal=GPIO_Input
PC6.GPIOParameters=GPIO_Label
PC6.GPIO_Label=YOUT0
PC6.Mode=Slave_8_bits_Embedded_Synchro
PC6.Signal=DCMI_D0
PC8.GPIOParameters=GPIO_Label
PC8.GPIO_Label=ADDR IN
PC8.Signal=GPIO_Output
PC9.GPIOParameters=GPIO_Label
PC9.GPIO_Label=YOUT3
PC9.Mode=Slave_8_bits_Embedded_Synchro
PC9.Signal=DCMI_D3
PD0.GPIOParameters=GPIO_PuPd,GPIO_Label
PD0.GPIO_Label=RAM nPD
PD0.GPIO_PuPd=GPIO_PULLUP
PD0.Signal=GPIO_Output
PD1.GPIOParameters=GPIO_PuPd,GPIO_Label
PD1.GPIO_Label=CAM PD
PD1.GPIO_PuPd=GPIO_PULLDOWN
PD1.Signal=GPIO_Output
PD10.GPIOParameters=GPIO_Label
PD10.GPIO_Label=LED B
PD10.Signal=GPIO_Output
PD11.GPIOParameters=GPIO_PuPd,GPIO_Label
PD11.GPIO_Label=ADDR nOE
PD11.GPIO_PuPd=GPIO_PULLUP
PD11.Signal=GPIO_Output
PD12.GPIOParameters=GPIO_PuPd,GPIO_Label
PD12.GPIO_Label=DATA nOE
PD12.GPIO_PuPd=GPIO_PULLUP
PD12.Signal=GPIO_Output
PD13.GPIOParameters=GPIO_Label
PD13.GPIO_Label=DATA CLK
PD13.Signal=GPIO_Output
PD14.GPIOParameters=GPIO_Label
PD14.GPIO_Label=DATA IN
PD14.Signal=GPIO_Output
PD15.GPIOParameters=GPIO_Label
PD15.GPIO_Label=ADDR CLK
PD15.Signal=GPIO_Output
PD2.GPIOParameters=GPIO_PuPd,GPIO_Label
PD2.GPIO_Label=SR nCLR
PD2.GPIO_PuPd=GPIO_PULLUP
PD2.Signal=GPIO_Output
PD3.GPIOParameters=GPIO_Label
PD3.GPIO_Label=YOUT5
PD3.Mode=Slave_8_bits_Embedded_Synchro
PD3.Signal=DCMI_D5
PD4.GPIOParameters=GPIO_PuPd,GPIO_Label
PD4.GPIO_Label=RAM nDQM
PD4.GPIO_PuPd=GPIO_PULLUP
PD4.Signal=GPIO_Output
PD5.GPIOParameters=GPIO_Label
PD5.GPIO_Label=RAM nWE
PD5.Signal=GPIO_Output
PD6.GPIOParameters=GPIO_PuPd,GPIO_Label
PD6.GPIO_Label=RAM nCAS
PD6.GPIO_PuPd=GPIO_PULLUP
PD6.Signal=GPIO_Output
PD7.GPIOParameters=GPIO_PuPd,GPIO_Label
PD7.GPIO_Label=RAM nRAS
PD7.GPIO_PuPd=GPIO_PULLUP
PD7.Signal=GPIO_Output
PD8.GPIOParameters=GPIO_Label
PD8.GPIO_Label=LED R
PD8.Signal=GPIO_Output
PD9.GPIOParameters=GPIO_Label
PD9.GPIO_Label=LED G
PD9.Signal=GPIO_Output
PE10.GPIOParameters=GPIO_Label
PE10.GPIO_Label=EEPROM nWC
PE10.Signal=GPIO_Output
PE11.GPIOParameters=GPIO_Label
PE11.GPIO_Label=QSPI nCS
PE11.Signal=GPIO_Output
PE12.GPIOParameters=GPIO_PuPd,GPIO_Label
PE12.GPIO_Label=DIP 7
PE12.GPIO_PuPd=GPIO_PULLDOWN
PE12.Signal=GPIO_Input
PE13.GPIOParameters=GPIO_PuPd,GPIO_Label
PE13.GPIO_Label=DIP 8
PE13.GPIO_PuPd=GPIO_PULLDOWN
PE13.Signal=GPIO_Input
PE14.GPIOParameters=GPIO_PuPd,GPIO_Label
PE14.GPIO_Label=DIP 9
PE14.GPIO_PuPd=GPIO_PULLDOWN
PE14.Signal=GPIO_Input
PE15.GPIOParameters=GPIO_PuPd,GPIO_Label
PE15.GPIO_Label=DIP 10
PE15.GPIO_PuPd=GPIO_PULLDOWN
PE15.Signal=GPIO_Input
PE2.GPIOParameters=GPIO_Label
PE2.GPIO_Label=QSPI IO2
PE2.Mode=OCTOSPI2_IOL_Port1L
PE2.Signal=OCTOSPIM_P1_IO2
PE4.GPIOParameters=GPIO_Label
PE4.GPIO_Label=YOUT4
PE4.Mode=Slave_8_bits_Embedded_Synchro
PE4.Signal=DCMI_D4
PE5.GPIOParameters=GPIO_Label
PE5.GPIO_Label=YOUT6
PE5.Mode=Slave_8_bits_Embedded_Synchro
PE5.Signal=DCMI_D6
PE6.GPIOParameters=GPIO_Label
PE6.GPIO_Label=YOUT7
PE6.Mode=Slave_8_bits_Embedded_Synchro
PE6.Signal=DCMI_D7
PE9.GPIOParameters=GPIO_Label
PE9.GPIO_Label=HDMI CLK
PE9.Signal=S_TIM1_CH1
PH0-OSC_IN.GPIOParameters=GPIO_Label
PH0-OSC_IN.GPIO_Label=HSE OSC
PH0-OSC_IN.Mode=HSE-External-Clock-Source
PH0-OSC_IN.Signal=RCC_OSC_IN
RCC.HSE_VALUE=50000000
RCC.SYSCLKFreq_VALUE=50000000
RCC.SYSCLKSource=RCC_SYSCLKSOURCE_HSE
board=custom

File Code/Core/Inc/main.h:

/* USER CODE BEGIN Header */
/**
  ******************************************************************************
  * @file           : main.h
  * @brief          : Header for main.c file.
  *                   This file contains the common defines of the application.
  ******************************************************************************
  * @attention
  *
  * Copyright (c) 2024 STMicroelectronics.
  * All rights reserved.
  *
  * This software is licensed under terms that can be found in the LICENSE file
  * in the root directory of this software component.
  * If no LICENSE file comes with this software, it is provided AS-IS.
  *
  ******************************************************************************
  */
/* USER CODE END Header */

/* Define to prevent recursive inclusion -------------------------------------*/
#ifndef __MAIN_H
#define __MAIN_H

#ifdef __cplusplus
extern "C" {
#endif

/* Includes ------------------------------------------------------------------*/
#include "stm32h7xx_hal.h"

/* Private includes ----------------------------------------------------------*/
/* USER CODE BEGIN Includes */

/* USER CODE END Includes */

/* Exported types ------------------------------------------------------------*/
/* USER CODE BEGIN ET */

/* USER CODE END ET */

/* Exported constants --------------------------------------------------------*/
/* USER CODE BEGIN EC */

/* USER CODE END EC */

/* Exported macro ------------------------------------------------------------*/
/* USER CODE BEGIN EM */

/* USER CODE END EM */

void HAL_TIM_MspPostInit(TIM_HandleTypeDef *htim);

/* Exported functions prototypes ---------------------------------------------*/
void Error_Handler(void);

/* USER CODE BEGIN EFP */

/* USER CODE END EFP */

/* Private defines -----------------------------------------------------------*/
#define QSPI_IO2_Pin GPIO_PIN_2
#define QSPI_IO2_GPIO_Port GPIOE
#define YOUT4_Pin GPIO_PIN_4
#define YOUT4_GPIO_Port GPIOE
#define YOUT6_Pin GPIO_PIN_5
#define YOUT6_GPIO_Port GPIOE
#define YOUT7_Pin GPIO_PIN_6
#define YOUT7_GPIO_Port GPIOE
#define LSE_OSC_Pin GPIO_PIN_14
#define LSE_OSC_GPIO_Port GPIOC
#define HSE_OSC_Pin GPIO_PIN_0
#define HSE_OSC_GPIO_Port GPIOH
#define DIP_1_Pin GPIO_PIN_0
#define DIP_1_GPIO_Port GPIOC
#define DIP_3_Pin GPIO_PIN_2
#define DIP_3_GPIO_Port GPIOC
#define DIP_4_Pin GPIO_PIN_3
#define DIP_4_GPIO_Port GPIOC
#define I2S_WS_Pin GPIO_PIN_0
#define I2S_WS_GPIO_Port GPIOA
#define QSPI_IO3_Pin GPIO_PIN_1
#define QSPI_IO3_GPIO_Port GPIOA
#define DAC_nCS_Pin GPIO_PIN_4
#define DAC_nCS_GPIO_Port GPIOA
#define I2S_SCK_Pin GPIO_PIN_5
#define I2S_SCK_GPIO_Port GPIOA
#define CAM_CLK_Pin GPIO_PIN_6
#define CAM_CLK_GPIO_Port GPIOA
#define RAM_CLK_Pin GPIO_PIN_7
#define RAM_CLK_GPIO_Port GPIOA
#define DIP_5_Pin GPIO_PIN_4
#define DIP_5_GPIO_Port GPIOC
#define DIP_6_Pin GPIO_PIN_5
#define DIP_6_GPIO_Port GPIOC
#define QSPI_IO1_Pin GPIO_PIN_0
#define QSPI_IO1_GPIO_Port GPIOB
#define QSPI_IO0_Pin GPIO_PIN_1
#define QSPI_IO0_GPIO_Port GPIOB
#define QSPI_CLK_Pin GPIO_PIN_2
#define QSPI_CLK_GPIO_Port GPIOB
#define HDMI_CLK_Pin GPIO_PIN_9
#define HDMI_CLK_GPIO_Port GPIOE
#define EEPROM_nWC_Pin GPIO_PIN_10
#define EEPROM_nWC_GPIO_Port GPIOE
#define QSPI_nCS_Pin GPIO_PIN_11
#define QSPI_nCS_GPIO_Port GPIOE
#define DIP_7_Pin GPIO_PIN_12
#define DIP_7_GPIO_Port GPIOE
#define DIP_8_Pin GPIO_PIN_13
#define DIP_8_GPIO_Port GPIOE
#define DIP_9_Pin GPIO_PIN_14
#define DIP_9_GPIO_Port GPIOE
#define DIP_10_Pin GPIO_PIN_15
#define DIP_10_GPIO_Port GPIOE
#define I2S_SCL_Pin GPIO_PIN_10
#define I2S_SCL_GPIO_Port GPIOB
#define I2C_SDA_Pin GPIO_PIN_11
#define I2C_SDA_GPIO_Port GPIOB
#define I2S_MCLK_CTRL_Pin GPIO_PIN_12
#define I2S_MCLK_CTRL_GPIO_Port GPIOB
#define YOUT2_Pin GPIO_PIN_13
#define YOUT2_GPIO_Port GPIOB
#define HDMI_INT_Pin GPIO_PIN_14
#define HDMI_INT_GPIO_Port GPIOB
#define nREC_Pin GPIO_PIN_15
#define nREC_GPIO_Port GPIOB
#define LED_R_Pin GPIO_PIN_8
#define LED_R_GPIO_Port GPIOD
#define LED_G_Pin GPIO_PIN_9
#define LED_G_GPIO_Port GPIOD
#define LED_B_Pin GPIO_PIN_10
#define LED_B_GPIO_Port GPIOD
#define ADDR_nOE_Pin GPIO_PIN_11
#define ADDR_nOE_GPIO_Port GPIOD
#define DATA_nOE_Pin GPIO_PIN_12
#define DATA_nOE_GPIO_Port GPIOD
#define DATA_CLK_Pin GPIO_PIN_13
#define DATA_CLK_GPIO_Port GPIOD
#define DATA_IN_Pin GPIO_PIN_14
#define DATA_IN_GPIO_Port GPIOD
#define ADDR_CLK_Pin GPIO_PIN_15
#define ADDR_CLK_GPIO_Port GPIOD
#define YOUT0_Pin GPIO_PIN_6
#define YOUT0_GPIO_Port GPIOC
#define ADDR_IN_Pin GPIO_PIN_8
#define ADDR_IN_GPIO_Port GPIOC
#define YOUT3_Pin GPIO_PIN_9
#define YOUT3_GPIO_Port GPIOC
#define USB_VBUS_Pin GPIO_PIN_9
#define USB_VBUS_GPIO_Port GPIOA
#define YOUT1_Pin GPIO_PIN_10
#define YOUT1_GPIO_Port GPIOA
#define USB_DM_Pin GPIO_PIN_11
#define USB_DM_GPIO_Port GPIOA
#define USB_DP_Pin GPIO_PIN_12
#define USB_DP_GPIO_Port GPIOA
#define SWDIO_Pin GPIO_PIN_13
#define SWDIO_GPIO_Port GPIOA
#define SWCLK_Pin GPIO_PIN_14
#define SWCLK_GPIO_Port GPIOA
#define HDMI_CE_Pin GPIO_PIN_15
#define HDMI_CE_GPIO_Port GPIOA
#define DAC_CLK_Pin GPIO_PIN_10
#define DAC_CLK_GPIO_Port GPIOC
#define DIP_2_Pin GPIO_PIN_11
#define DIP_2_GPIO_Port GPIOC
#define DAC_MOSI_Pin GPIO_PIN_12
#define DAC_MOSI_GPIO_Port GPIOC
#define RAM_nPD_Pin GPIO_PIN_0
#define RAM_nPD_GPIO_Port GPIOD
#define CAM_PD_Pin GPIO_PIN_1
#define CAM_PD_GPIO_Port GPIOD
#define SR_nCLR_Pin GPIO_PIN_2
#define SR_nCLR_GPIO_Port GPIOD
#define YOUT5_Pin GPIO_PIN_3
#define YOUT5_GPIO_Port GPIOD
#define RAM_nDQM_Pin GPIO_PIN_4
#define RAM_nDQM_GPIO_Port GPIOD
#define RAM_nWE_Pin GPIO_PIN_5
#define RAM_nWE_GPIO_Port GPIOD
#define RAM_nCAS_Pin GPIO_PIN_6
#define RAM_nCAS_GPIO_Port GPIOD
#define RAM_nRAS_Pin GPIO_PIN_7
#define RAM_nRAS_GPIO_Port GPIOD
#define SWO_Pin GPIO_PIN_3
#define SWO_GPIO_Port GPIOB
#define I2S_SD_Pin GPIO_PIN_4
#define I2S_SD_GPIO_Port GPIOB
#define OSD_A2_Pin GPIO_PIN_5
#define OSD_A2_GPIO_Port GPIOB
#define OSD_A1_Pin GPIO_PIN_6
#define OSD_A1_GPIO_Port GPIOB
#define OSD_A0_Pin GPIO_PIN_7
#define OSD_A0_GPIO_Port GPIOB
#define OSD_EN_Pin GPIO_PIN_8
#define OSD_EN_GPIO_Port GPIOB

/* USER CODE BEGIN Private defines */

/* USER CODE END Private defines */

#ifdef __cplusplus
}
#endif

#endif /* __MAIN_H */

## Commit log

2024-11-17 Pushing Kicad and code
2024-11-17 gitignore and readme
2024-11-18 Working on init section of camera board firmware
2024-11-19 More init lines, added osd control code
2025-02-08 Pushing to share current version
